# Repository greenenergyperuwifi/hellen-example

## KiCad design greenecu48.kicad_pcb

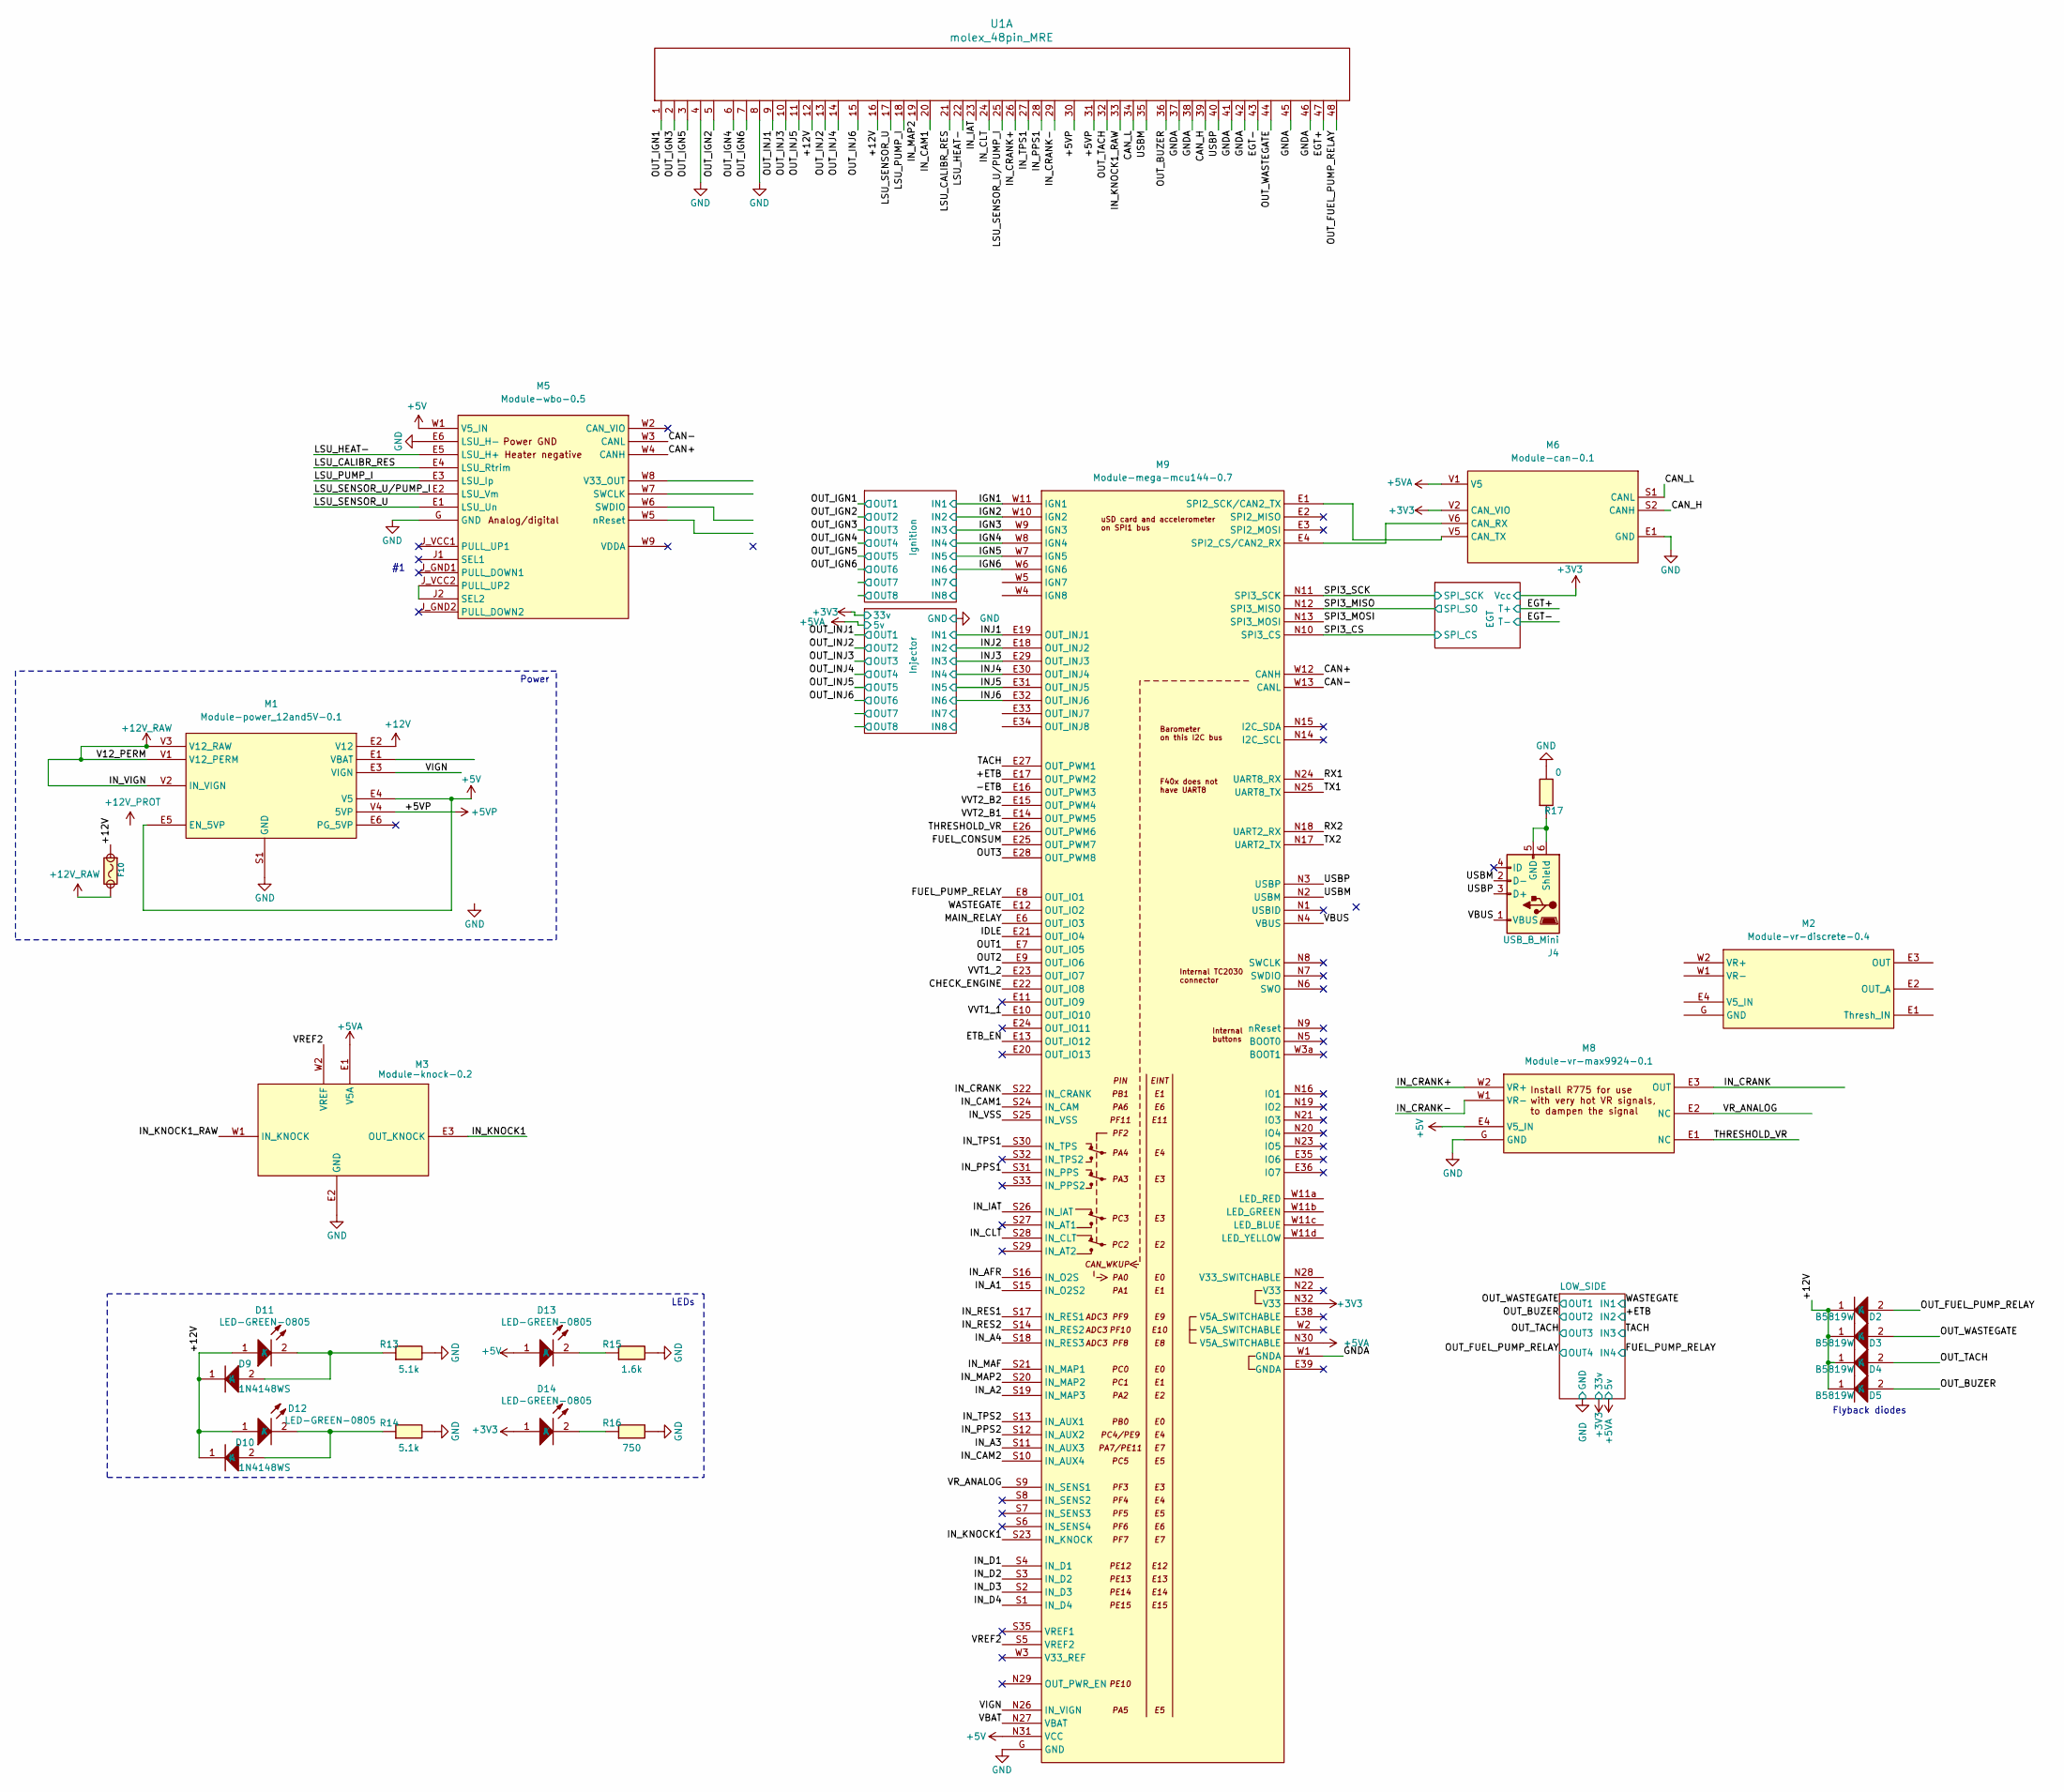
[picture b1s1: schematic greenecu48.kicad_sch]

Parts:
D2, D3, D4, D5: B5819W; SOD-123; LCSC C8598
D9, D10: 1N4148WS; SOD-323; LCSC C2128
D11, D12, D13, D14: LED-GREEN-0805; LED-0805; LCSC C2297
F10: Fuse-Pad-Pad; PAD-1206-PAD; LCSC C182446
J4: USB_B_Mini; USB-MINI-B-VERTICAL; LCSC C13453
M1: Module-power_12and5V-0.1; power_12and5V
M2: Module-vr-discrete-0.4; vr-discrete
M3: Module-knock-0.2; knock
M5: Module-wbo-0.5; wbo
M6: Module-can-0.1; can
M8: Module-vr-max9924-0.1; vr-max9924
M9: Module-mega-mcu144-0.7; mega-mcu144
R13, R14: 5.1k; R0603; LCSC C23186
R15: 1.6k; R0603; LCSC C22847
R16: 750; R0603; LCSC C23241
R17: 0; R0603; LCSC C21189
U1: molex_48pin_MRE; Molex_48_MRE; Part # 500762-0481; LCSC C164171

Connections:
+3V3: D14.1 (A), M6.V2 (CAN_VIO), M9.N32 (V33); also elsewhere on the board
+5V: D13.1 (A), M1.E4 (V5), M1.E5 (EN_5VP), M5.W1 (V5_IN), M8.E4 (V5_IN), M9.N31 (VCC)
+5VA: M3.E1 (V5A), M6.V1 (V5), M9.N30 (V5A_SWITCHABLE); also elsewhere on the board
+5VP: M1.V4 (5VP), U1.30, U1.31
+12V: D2.1 (K), D3.1 (K), D4.1 (K), D5.1 (K), D9.1 (K), D10.1 (K), D11.1 (A), D12.1 (A), F10.1, M1.E2 (V12), U1.12, U1.16
+12V_RAW: F10.2, M1.V1 (V12_PERM), M1.V2 (IN_VIGN), M1.V3 (V12_RAW)
/+ETB: M9.E17 (OUT_PWM2); also elsewhere on the board
/-ETB: M9.E16 (OUT_PWM3)
/CAN+: M5.W4 (CANH), M9.W12 (CANH)
/CAN-: M5.W3 (CANL), M9.W13 (CANL)
/CAN_H: M6.S2 (CANH), U1.39
/CAN_L: M6.S1 (CANL), U1.34
/CHECK_ENGINE: M9.E22 (OUT_IO8)
/EGT+: U1.47; also elsewhere on the board
/EGT-: U1.43; also elsewhere on the board
/ETB_EN: M9.E13 (OUT_IO12)
/FUEL_CONSUM: M9.E25 (OUT_PWM7)
/FUEL_PUMP_RELAY: M9.E8 (OUT_IO1); also elsewhere on the board
/GNDA: M9.W1 (GNDA), U1.37, U1.38, U1.41, U1.42, U1.45, U1.46
/IDLE: M9.E21 (OUT_IO4)
/IGN1: M9.W11 (IGN1); also elsewhere on the board
/IGN2: M9.W10 (IGN2); also elsewhere on the board
/IGN3: M9.W9 (IGN3); also elsewhere on the board
/IGN4: M9.W8 (IGN4); also elsewhere on the board
/IGN5: M9.W7 (IGN5); also elsewhere on the board
/IGN6: M9.W6 (IGN6); also elsewhere on the board
/INJ1: M9.E19 (OUT_INJ1); also elsewhere on the board
/INJ2: M9.E18 (OUT_INJ2); also elsewhere on the board
/INJ3: M9.E29 (OUT_INJ3); also elsewhere on the board
/INJ4: M9.E30 (OUT_INJ4); also elsewhere on the board
/INJ5: M9.E31 (OUT_INJ5); also elsewhere on the board
/INJ6: M9.E32 (OUT_INJ6); also elsewhere on the board
/IN_A1: M9.S15 (IN_O2S2)
/IN_A2: M9.S19 (IN_MAP3)
/IN_A3: M9.S11 (IN_AUX3)
/IN_A4: M9.S18 (IN_RES3)
/IN_AFR: M9.S16 (IN_O2S)
/IN_CAM1: M9.S24 (IN_CAM), U1.20
/IN_CAM2: M9.S10 (IN_AUX4)
/IN_CLT: M9.S28 (IN_CLT), U1.24
/IN_CRANK: M8.E3 (OUT), M9.S22 (IN_CRANK)
/IN_CRANK+: M8.W2 (VR+), U1.26
/IN_CRANK-: M8.W1 (VR-), U1.29
/IN_D1: M9.S4 (IN_D1)
/IN_D2: M9.S3 (IN_D2)
/IN_D3: M9.S2 (IN_D3)
/IN_D4: M9.S1 (IN_D4)
/IN_IAT: M9.S26 (IN_IAT), U1.23
/IN_KNOCK1: M3.E3 (OUT_KNOCK), M9.S23 (IN_KNOCK)
/IN_KNOCK1_RAW: M3.W1 (IN_KNOCK), U1.33
/IN_MAF: M9.S21 (IN_MAP1)
/IN_MAP2: M9.S20 (IN_MAP2), U1.19
/IN_PPS1: M9.S31 (IN_PPS), U1.28
/IN_PPS2: M9.S12 (IN_AUX2)
/IN_RES1: M9.S17 (IN_RES1)
/IN_RES2: M9.S14 (IN_RES2)
/IN_TPS1: M9.S30 (IN_TPS), U1.27
/IN_TPS2: M9.S13 (IN_AUX1)
/IN_VSS: M9.S25 (IN_VSS)
/LSU_CALIBR_RES: M5.E4 (LSU_Rtrim), U1.21
/LSU_HEAT-: M5.E5 (LSU_H+), U1.22
/LSU_PUMP_I: M5.E3 (LSU_Ip), U1.18
/LSU_SENSOR_U: M5.E1 (LSU_Un), U1.17
/LSU_SENSOR_U/PUMP_I: M5.E2 (LSU_Vm), U1.25
/MAIN_RELAY: M9.E6 (OUT_IO3)
/OUT1: M9.E7 (OUT_IO5)
/OUT2: M9.E9 (OUT_IO6)
/OUT3: M9.E28 (OUT_PWM8)
/OUT_BUZER: D5.2 (A), U1.36; also elsewhere on the board
/OUT_FUEL_PUMP_RELAY: D2.2 (A), U1.48; also elsewhere on the board
/OUT_IGN1: U1.1; also elsewhere on the board
/OUT_IGN2: U1.5; also elsewhere on the board
/OUT_IGN3: U1.2; also elsewhere on the board
/OUT_IGN4: U1.6; also elsewhere on the board
/OUT_IGN5: U1.3; also elsewhere on the board
/OUT_IGN6: U1.7; also elsewhere on the board
/OUT_INJ1: U1.9; also elsewhere on the board
/OUT_INJ2: U1.13; also elsewhere on the board
/OUT_INJ3: U1.10; also elsewhere on the board
/OUT_INJ4: U1.14; also elsewhere on the board
/OUT_INJ5: U1.11; also elsewhere on the board
/OUT_INJ6: U1.15; also elsewhere on the board
/OUT_TACH: D4.2 (A), U1.32; also elsewhere on the board
/OUT_WASTEGATE: D3.2 (A), U1.44; also elsewhere on the board
/RX1: M9.N24 (UART8_RX)
/RX2: M9.N18 (UART2_RX)
/SPI3_CS: M9.N10 (SPI3_CS); also elsewhere on the board
/SPI3_MISO: M9.N12 (SPI3_MISO); also elsewhere on the board
/SPI3_MOSI: M9.N13 (SPI3_MOSI)
/SPI3_SCK: M9.N11 (SPI3_SCK); also elsewhere on the board
/TACH: M9.E27 (OUT_PWM1); also elsewhere on the board
/THRESHOLD_VR: M8.E1 (NC), M9.E26 (OUT_PWM6)
/TX1: M9.N25 (UART8_TX)
/TX2: M9.N17 (UART2_TX)
/USBM: J4.2 (D-), M9.N2 (USBM), U1.35
/USBP: J4.3 (D+), M9.N3 (USBP), U1.40
/VBAT: M9.N27 (VBAT)
/VBUS: J4.1 (VBUS), M9.N4 (VBUS)
/VIGN: M1.E3 (VIGN), M9.N26 (IN_VIGN)
/VREF2: M3.W2 (VREF), M9.S5 (VREF2)
/VR_ANALOG: M8.E2 (NC), M9.S9 (IN_SENS1)
/VVT1_1: M9.E10 (OUT_IO10)
/VVT1_2: M9.E23 (OUT_IO7)
/VVT2_B1: M9.E14 (OUT_PWM5)
/VVT2_B2: M9.E15 (OUT_PWM4)
/WASTEGATE: M9.E12 (OUT_IO2); also elsewhere on the board
GND: M1.S1 (GND), M3.E2 (GND), M5.E6 (LSU_H-), M5.G (GND), M6.E1 (GND), M8.G (GND), M9.G (GND), R13.2, R14.2, R15.2, R16.2, R17.2, U1.4, U1.8; also elsewhere on the board
unnamed: D10.2 (A), D12.2 (K), R14.1
unnamed: D9.2 (A), D11.2 (K), R13.1
unnamed: D13.2 (K), R15.1
unnamed: D14.2 (K), R16.1
unnamed: J4.5 (GND), J4.6 (Shield), R17.1
unnamed: M5.J2 (SEL2), M5.J_VCC2 (PULL_UP2)
unnamed: M6.V6 (CAN_RX), M9.E4 (SPI2_CS/CAN2_RX)
unnamed: M6.V5 (CAN_TX), M9.E1 (SPI2_SCK/CAN2_TX)

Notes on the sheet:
Flyback diodes
LEDs
Power

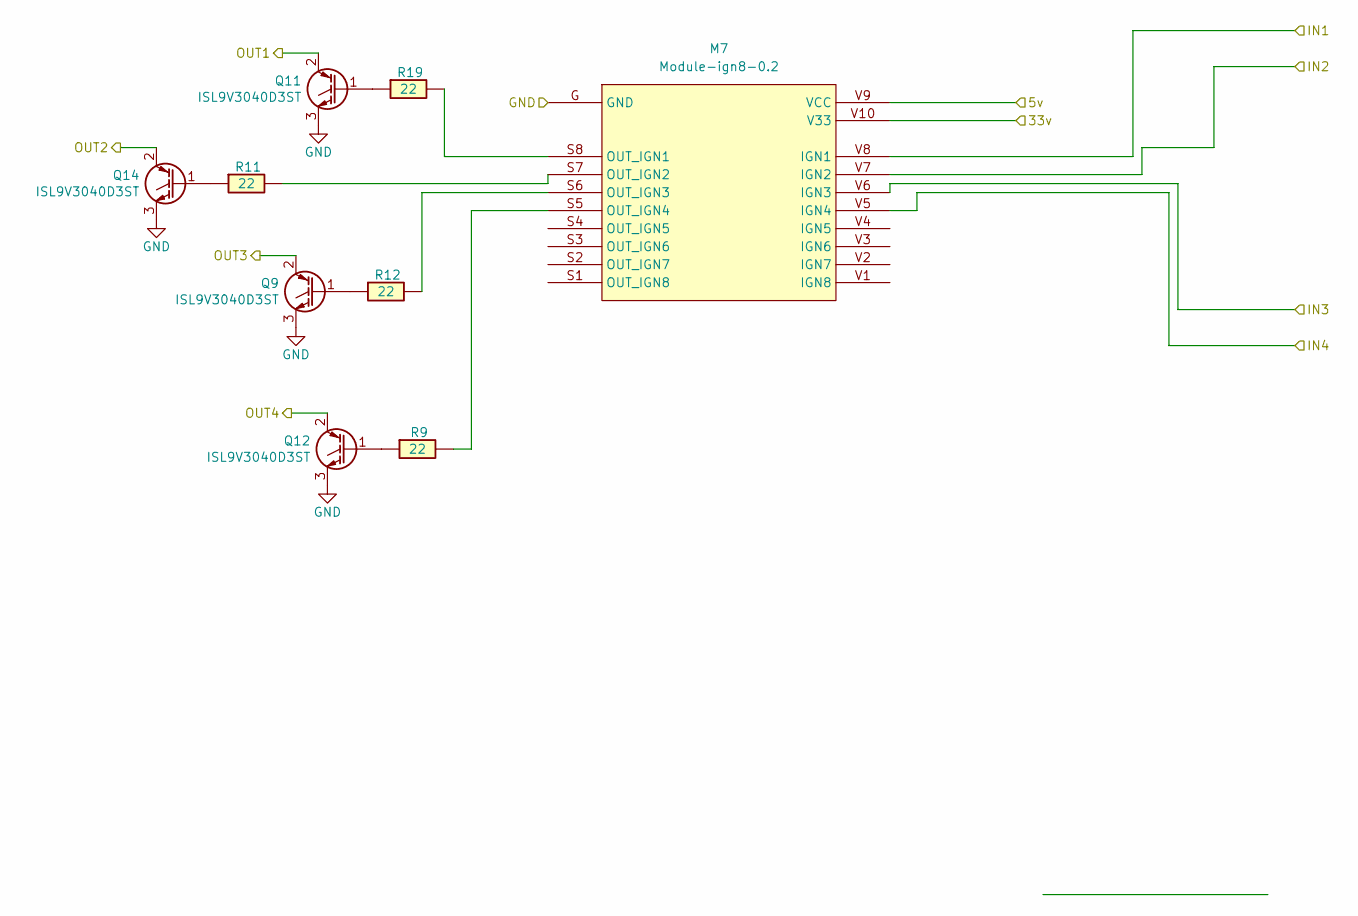
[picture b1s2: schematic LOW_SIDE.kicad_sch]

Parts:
M7: Module-ign8-0.2; ign8
Q9, Q11, Q12, Q14: ISL9V3040D3ST; TO-252-2; LCSC C5350881
R9, R11, R12, R19: 22; R0603; LCSC C23345

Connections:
+3V3: M7.V10 (V33); also elsewhere on the board
+5VA: M7.V9 (VCC); also elsewhere on the board
/+ETB: M7.V7 (IGN2); also elsewhere on the board
/FUEL_PUMP_RELAY: M7.V5 (IGN4); also elsewhere on the board
/OUT_BUZER: Q14.2 (C); also elsewhere on the board
/OUT_FUEL_PUMP_RELAY: Q12.2 (C); also elsewhere on the board
/OUT_TACH: Q9.2 (C); also elsewhere on the board
/OUT_WASTEGATE: Q11.2 (C); also elsewhere on the board
/TACH: M7.V6 (IGN3); also elsewhere on the board
/WASTEGATE: M7.V8 (IGN1); also elsewhere on the board
GND: M7.G (GND), Q9.3 (E), Q11.3 (E), Q12.3 (E), Q14.3 (E); also elsewhere on the board
unnamed: M7.S8 (OUT_IGN1), R19.2
unnamed: M7.S7 (OUT_IGN2), R11.2
unnamed: M7.S6 (OUT_IGN3), R12.2
unnamed: M7.S5 (OUT_IGN4), R9.2
unnamed: Q9.1 (G), R12.1
unnamed: Q11.1 (G), R19.1
unnamed: Q12.1 (G), R9.1
unnamed: Q14.1 (G), R11.1

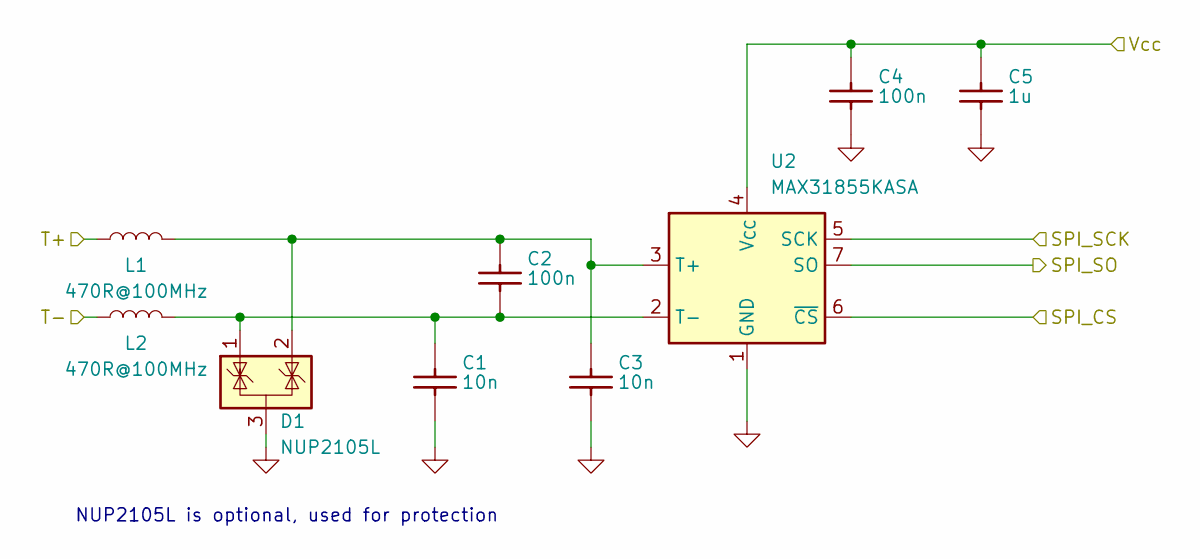
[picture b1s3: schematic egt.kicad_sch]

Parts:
C1, C3: 10n; C0603; LCSC C57112
C2, C4: 100n; C0603; LCSC C14663
C5: 1u; C0603; LCSC C15849
D1: NUP2105L; SOT-23; LCSC C284104
L1, L2: 470R@100MHz; L_0603_1608Metric; LCSC C97853
U2: MAX31855KASA; SOIC-8_3.9x4.9mm_P1.27mm; LCSC C52028

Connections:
+3V3: C4.2, C5.2, U2.4 (V_{CC}); also elsewhere on the board
/EGT+: L1.1; also elsewhere on the board
/EGT-: L2.1; also elsewhere on the board
/SPI3_CS: U2.6 (~CS); also elsewhere on the board
/SPI3_MISO: U2.7 (SO); also elsewhere on the board
/SPI3_SCK: U2.5 (SCK); also elsewhere on the board
GND: C1.1, C3.1, C4.1, C5.1, D1.3 (A), U2.1 (GND); also elsewhere on the board
unnamed: C2.2, C3.2, D1.2 (K), L1.2, U2.3 (T+)
unnamed: C1.2, C2.1, D1.1 (K), L2.2, U2.2 (T-)

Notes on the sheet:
NUP2105L is optional, used for protection

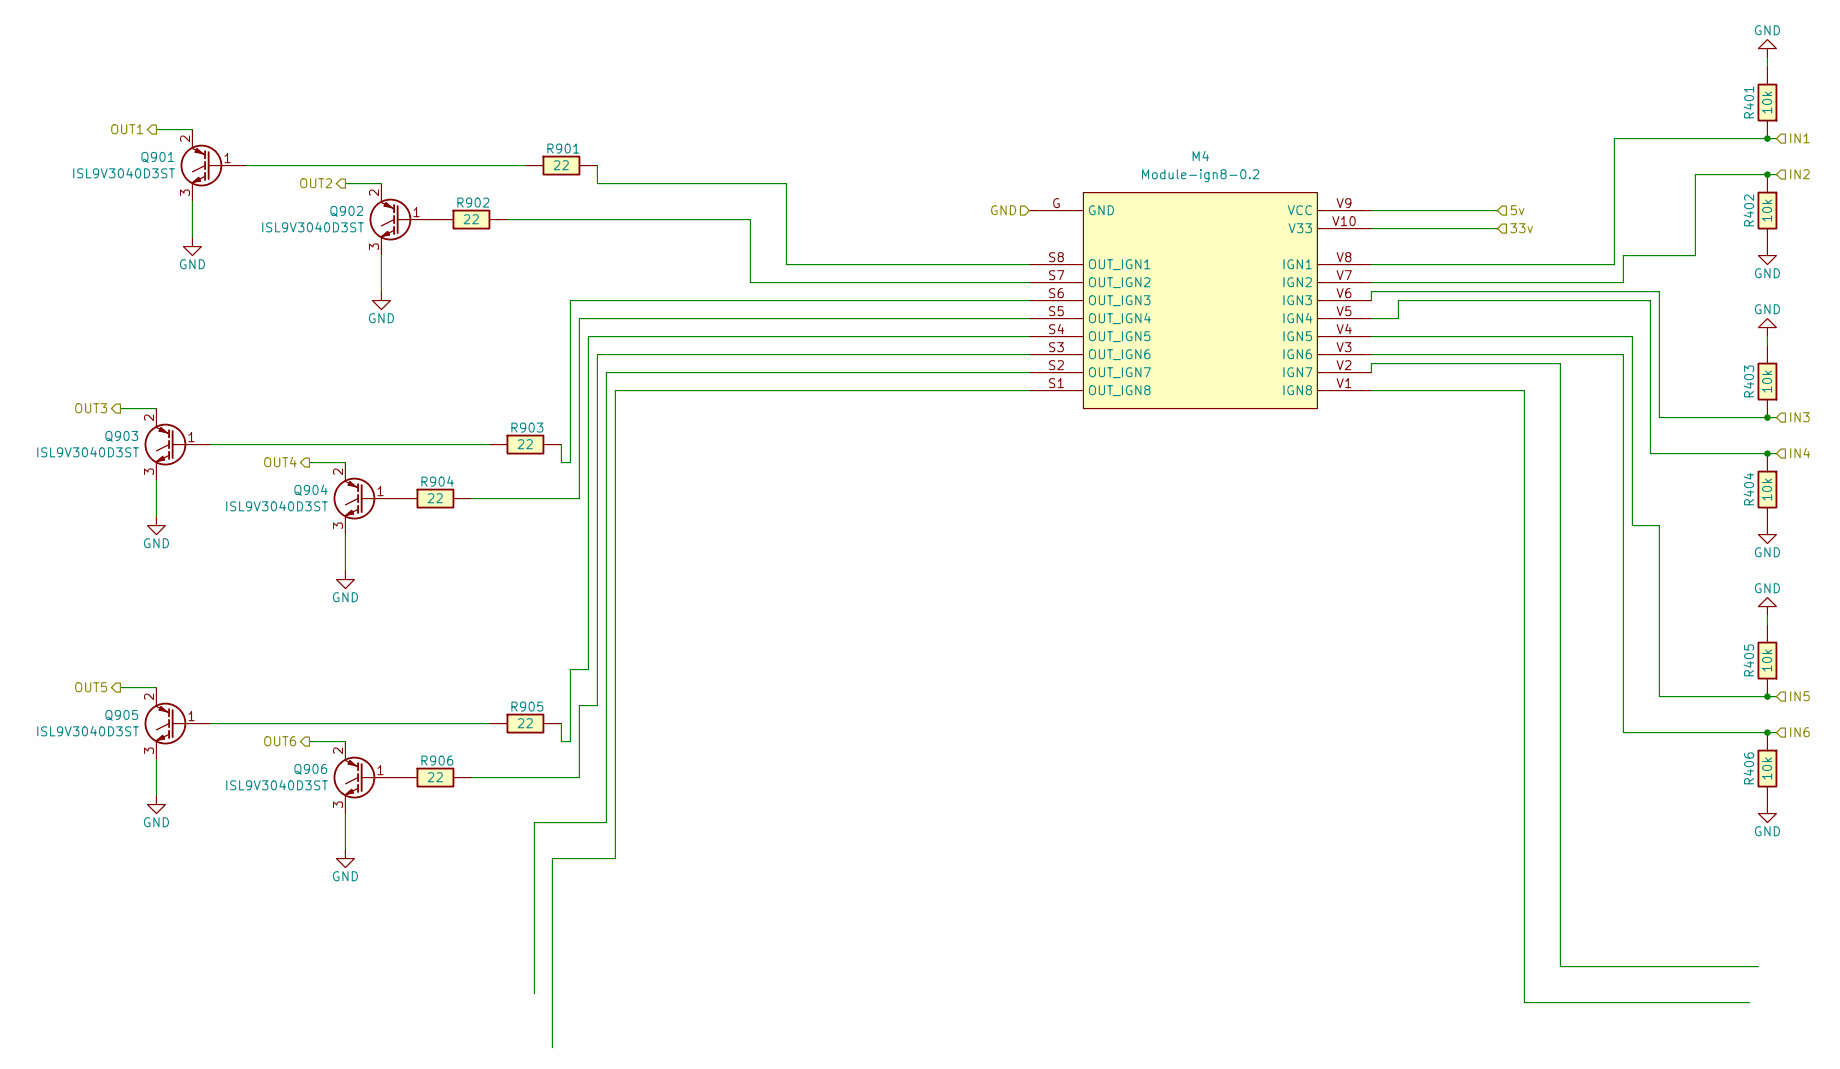
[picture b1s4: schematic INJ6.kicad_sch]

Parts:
M4: Module-ign8-0.2; ign8
Q901, Q902, Q903, Q904, Q905, Q906: ISL9V3040D3ST; TO-252-2; LCSC C5350881
R401, R402, R403, R404, R405, R406: 10k; R0603; LCSC C17414
R901, R902, R903, R904, R905, R906: 22; R0603; LCSC C23345

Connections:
+3V3: M4.V10 (V33); also elsewhere on the board
+5VA: M4.V9 (VCC); also elsewhere on the board
/INJ1: M4.V8 (IGN1), R401.1; also elsewhere on the board
/INJ2: M4.V7 (IGN2), R402.1; also elsewhere on the board
/INJ3: M4.V6 (IGN3), R403.1; also elsewhere on the board
/INJ4: M4.V5 (IGN4), R404.1; also elsewhere on the board
/INJ5: M4.V4 (IGN5), R405.1; also elsewhere on the board
/INJ6: M4.V3 (IGN6), R406.1; also elsewhere on the board
/OUT_INJ1: Q901.2 (C); also elsewhere on the board
/OUT_INJ2: Q902.2 (C); also elsewhere on the board
/OUT_INJ3: Q903.2 (C); also elsewhere on the board
/OUT_INJ4: Q904.2 (C); also elsewhere on the board
/OUT_INJ5: Q905.2 (C); also elsewhere on the board
/OUT_INJ6: Q906.2 (C); also elsewhere on the board
GND: M4.G (GND), Q901.3 (E), Q902.3 (E), Q903.3 (E), Q904.3 (E), Q905.3 (E), Q906.3 (E), R401.2, R402.2, R403.2, R404.2, R405.2, R406.2; also elsewhere on the board
unnamed: M4.S8 (OUT_IGN1), R901.2
unnamed: M4.S7 (OUT_IGN2), R902.2
unnamed: M4.S6 (OUT_IGN3), R903.2
unnamed: M4.S5 (OUT_IGN4), R904.2
unnamed: M4.S4 (OUT_IGN5), R905.2
unnamed: M4.S3 (OUT_IGN6), R906.2
unnamed: Q901.1 (G), R901.1
unnamed: Q902.1 (G), R902.1
unnamed: Q903.1 (G), R903.1
unnamed: Q904.1 (G), R904.1
unnamed: Q905.1 (G), R905.1
unnamed: Q906.1 (G), R906.1

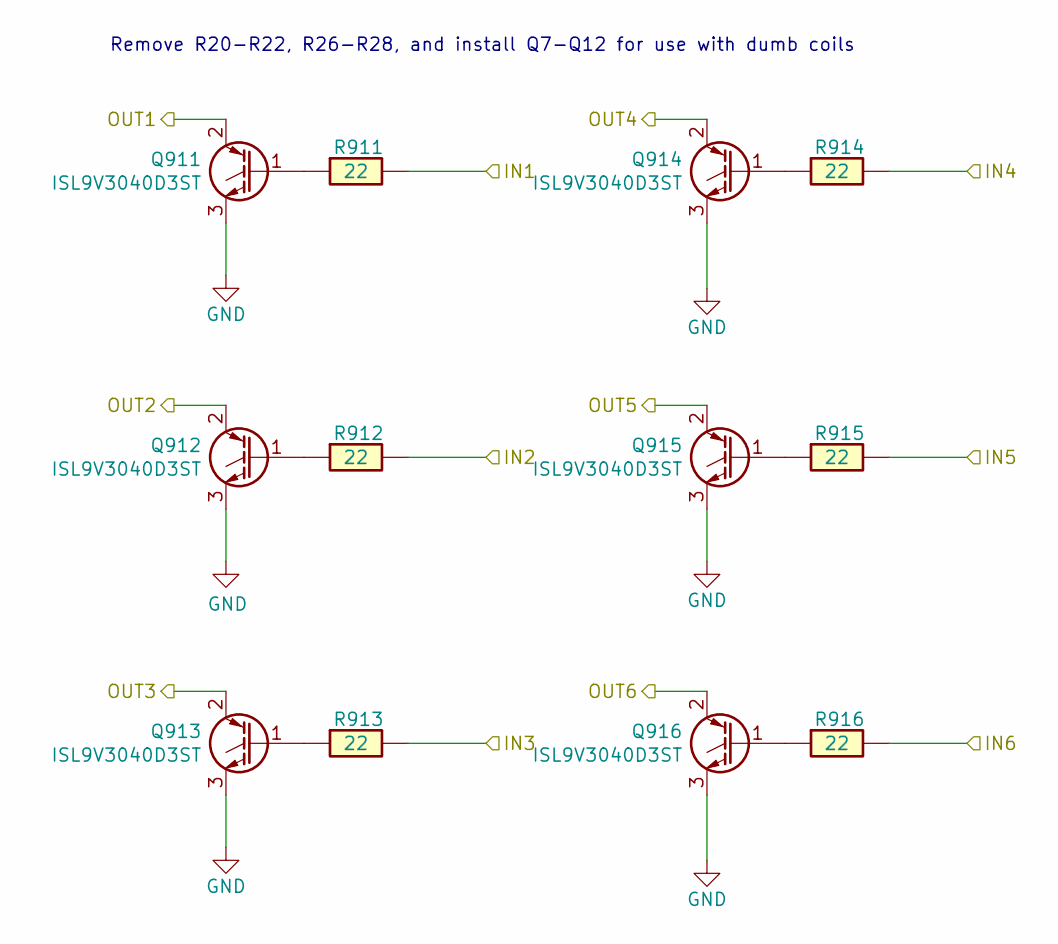
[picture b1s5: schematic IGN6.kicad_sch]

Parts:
Q911, Q912, Q913, Q914, Q915, Q916: ISL9V3040D3ST; TO-252-2; LCSC C462128
R911, R912, R913, R914, R915, R916: 22; R0603; LCSC C23345

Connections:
/IGN1: R911.2; also elsewhere on the board
/IGN2: R912.2; also elsewhere on the board
/IGN3: R913.2; also elsewhere on the board
/IGN4: R914.2; also elsewhere on the board
/IGN5: R915.2; also elsewhere on the board
/IGN6: R916.2; also elsewhere on the board
/OUT_IGN1: Q911.2 (C); also elsewhere on the board
/OUT_IGN2: Q912.2 (C); also elsewhere on the board
/OUT_IGN3: Q913.2 (C); also elsewhere on the board
/OUT_IGN4: Q914.2 (C); also elsewhere on the board
/OUT_IGN5: Q915.2 (C); also elsewhere on the board
/OUT_IGN6: Q916.2 (C); also elsewhere on the board
GND: Q911.3 (E), Q912.3 (E), Q913.3 (E), Q914.3 (E), Q915.3 (E), Q916.3 (E); also elsewhere on the board
unnamed: Q911.1 (G), R911.1
unnamed: Q912.1 (G), R912.1
unnamed: Q913.1 (G), R913.1
unnamed: Q914.1 (G), R914.1
unnamed: Q915.1 (G), R915.1
unnamed: Q916.1 (G), R916.1

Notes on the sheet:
Remove R20-R22, R26-R28, and install Q7-Q12 for use with dumb coils

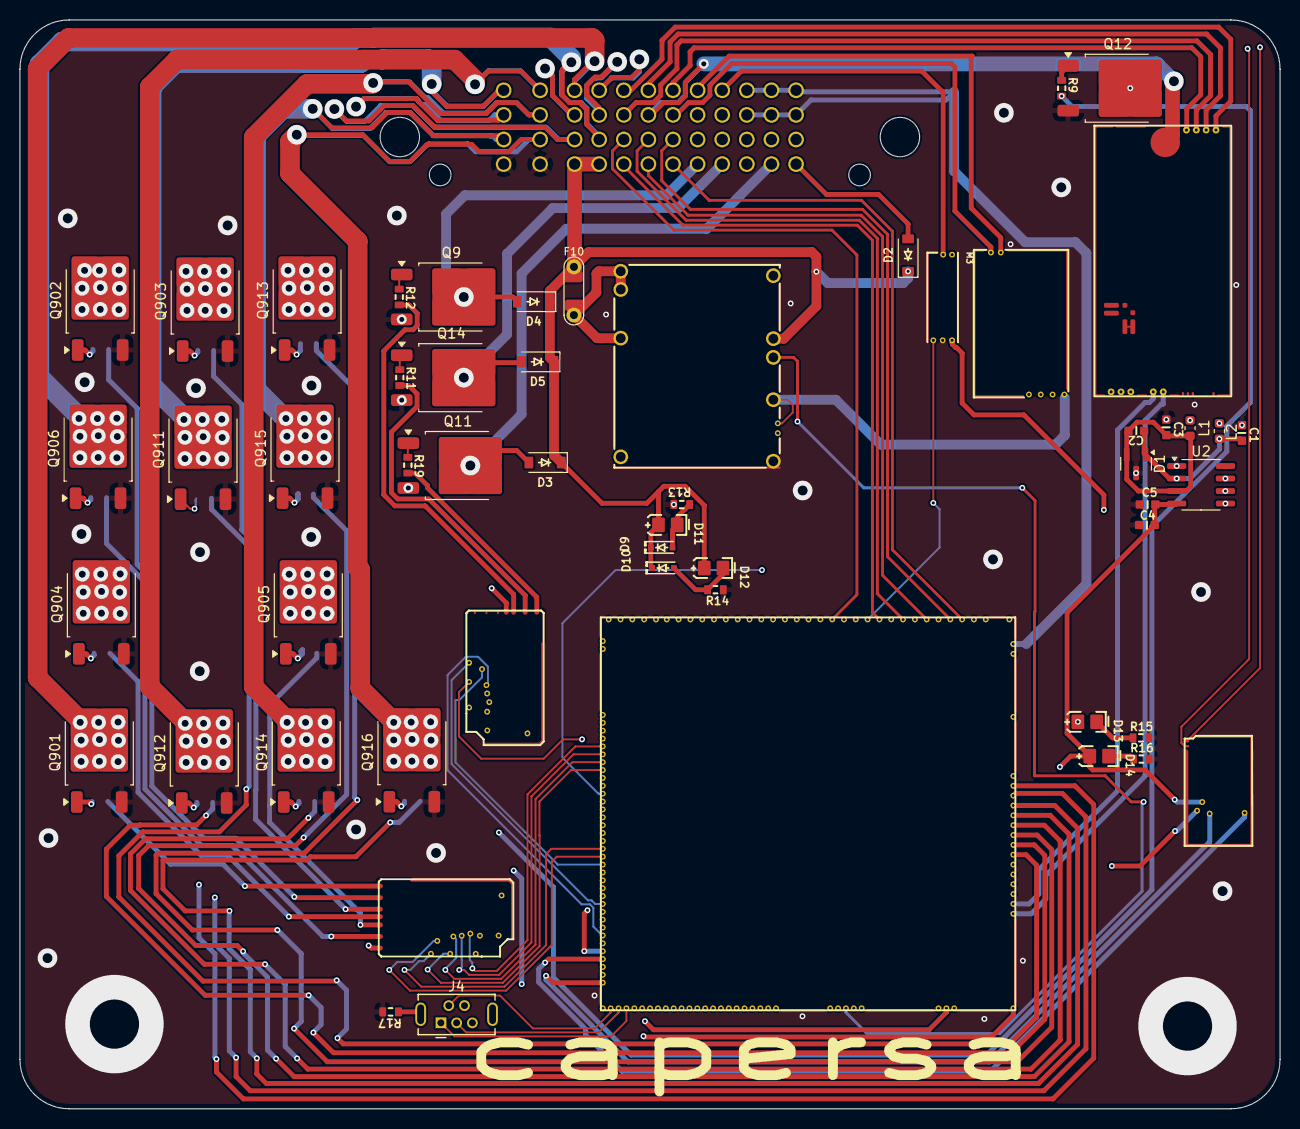
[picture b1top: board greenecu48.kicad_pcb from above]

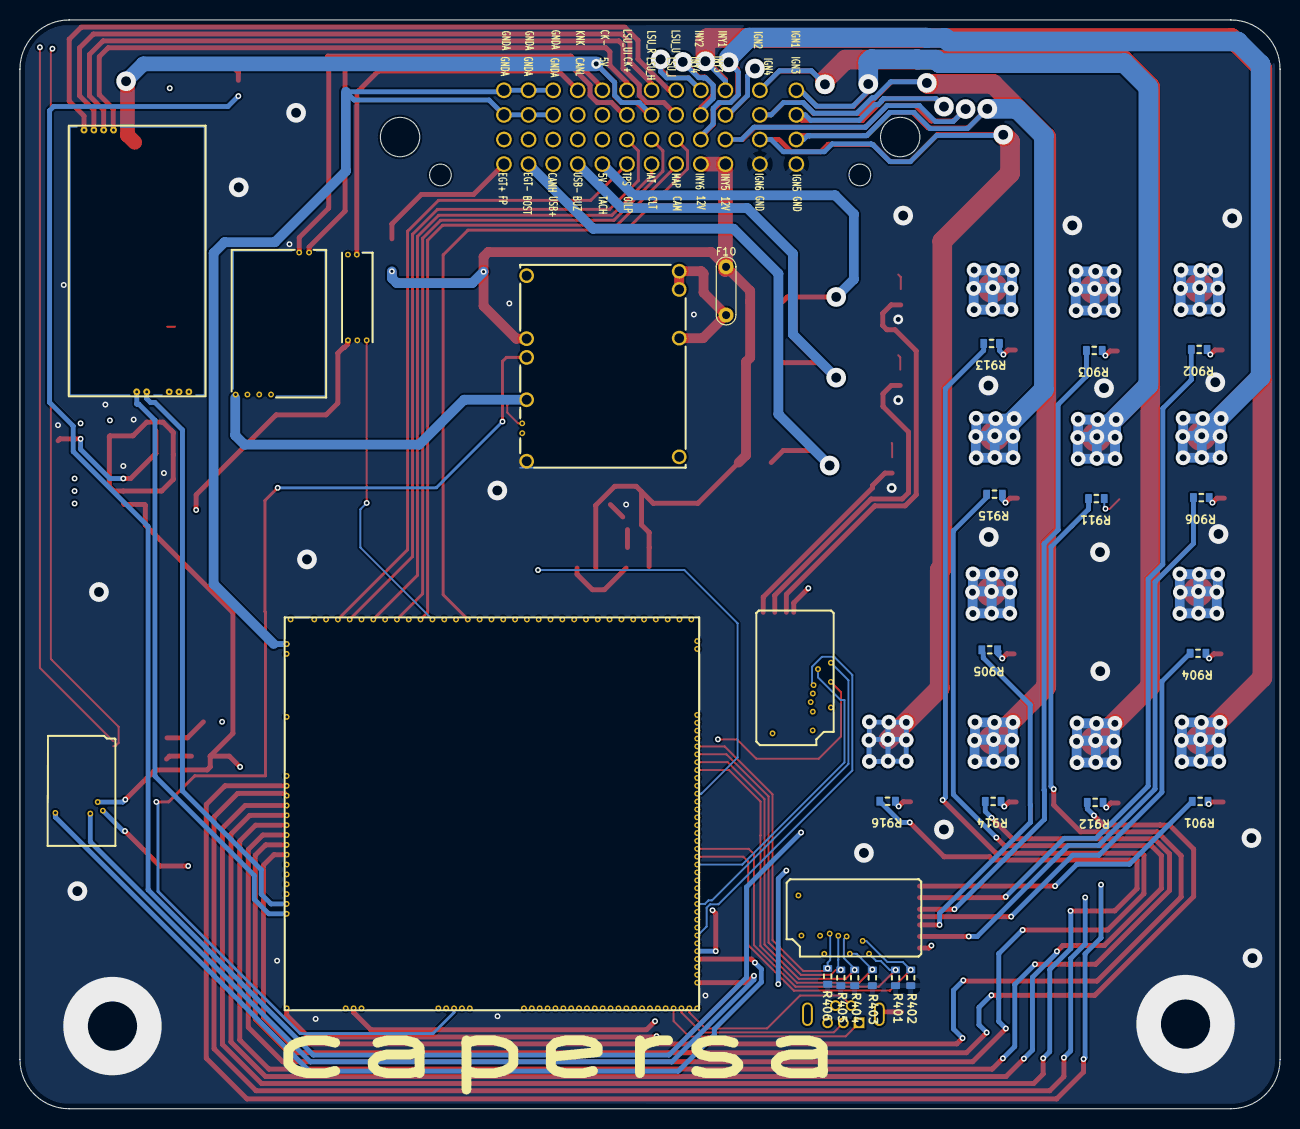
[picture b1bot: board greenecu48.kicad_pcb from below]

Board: 4 copper layers, 128.0 x 110.6 mm, 73 parts (18 on the bottom side), 108 nets.

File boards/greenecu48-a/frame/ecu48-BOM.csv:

Comment,Designator,Footprint,LCSC Part #
"10n","C1","C0603","C57112"
"100n","C2","C0603","C14663"
"10n","C3","C0603","C57112"
"100n","C4","C0603","C14663"
"1u","C5","C0603","C15849"
"NUP2105L","D1","SOT-23","C284104"
"B5819W","D2","SOD-123","C8598"
"B5819W","D3","SOD-123","C8598"
"B5819W","D4","SOD-123","C8598"
"B5819W","D5","SOD-123","C8598"
"1N4148WS","D9","SOD-323","C2128"
"1N4148WS","D10","SOD-323","C2128"
"LED-GREEN-0805","D11","LED-0805","C2297"
"LED-GREEN-0805","D12","LED-0805","C2297"
"LED-GREEN-0805","D13","LED-0805","C2297"
"LED-GREEN-0805","D14","LED-0805","C2297"
"Fuse-Pad-Pad","F10","PAD-1206-PAD","C182446"
"USB_B_Mini","J4","USB-MINI-B-VERTICAL","C13453"
"470R@100MHz","L1","L_0603_1608Metric","C97853"
"470R@100MHz","L2","L_0603_1608Metric","C97853"
"Module:power_12and5V/0.1","M1","power_12and5V",""
"Module:vr-discrete/0.4","M2","vr-discrete",""
"Module:knock/0.2","M3","knock",""
"Module:ign8/0.2","M4","ign8",""
"Module:wbo/0.5","M5","wbo",""
"Module:can/0.1","M6","can",""
"Module:ign8/0.2","M7","ign8",""
"Module:vr-max9924/0.1","M8","vr-max9924",""
"Module:mega-mcu144/0.7","M9","mega-mcu144",""
"ISL9V3040D3ST","Q9","DPAK","C5350881"
"ISL9V3040D3ST","Q11","DPAK","C5350881"
"ISL9V3040D3ST","Q12","DPAK","C5350881"
"ISL9V3040D3ST","Q14","DPAK","C5350881"
"ISL9V3040D3ST","Q901","DPAK","C5350881"
"ISL9V3040D3ST","Q902","DPAK","C5350881"
"ISL9V3040D3ST","Q903","DPAK","C5350881"
"ISL9V3040D3ST","Q904","DPAK","C5350881"
"ISL9V3040D3ST","Q905","DPAK","C5350881"
"ISL9V3040D3ST","Q906","DPAK","C5350881"
"ISL9V3040D3ST","Q911","DPAK","C462128"
"ISL9V3040D3ST","Q912","DPAK","C462128"
"ISL9V3040D3ST","Q913","DPAK","C462128"
"ISL9V3040D3ST","Q914","DPAK","C462128"
"ISL9V3040D3ST","Q915","DPAK","C462128"
"ISL9V3040D3ST","Q916","DPAK","C462128"
"22","R9","R0603","C23345"
"22","R11","R0603","C23345"
"22","R12","R0603","C23345"
"5.1k","R13","R0603","C23186"
"5.1k","R14","R0603","C23186"
"1.6k","R15","R0603","C22847"
"750","R16","R0603","C23241"
"0","R17","R0603","C21189"
"22","R19","R0603","C23345"
"10k","R401","R0603","C17414"
"10k","R402","R0603","C17414"
"10k","R403","R0603","C17414"
"10k","R404","R0603","C17414"
"10k","R405","R0603","C17414"
"10k","R406","R0603","C17414"
"22","R901","R0603","C23345"
"22","R902","R0603","C23345"
"22","R903","R0603","C23345"
"22","R904","R0603","C23345"
"22","R905","R0603","C23345"
"22","R906","R0603","C23345"
"22","R911","R0603","C23345"
"22","R912","R0603","C23345"
"22","R913","R0603","C23345"
"22","R914","R0603","C23345"
"22","R915","R0603","C23345"
"22","R916","R0603","C23345"
"molex_48pin_MRE","U1","Molex_48_MRE","C164171"
"MAX31855KASA","U2","SO8","C52028"

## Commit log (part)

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2026-01-27 [skip actions] Auto-generated board v2.1
2026-01-28 wreew
2026-02-07 qwqwq
2026-02-09 gshw
